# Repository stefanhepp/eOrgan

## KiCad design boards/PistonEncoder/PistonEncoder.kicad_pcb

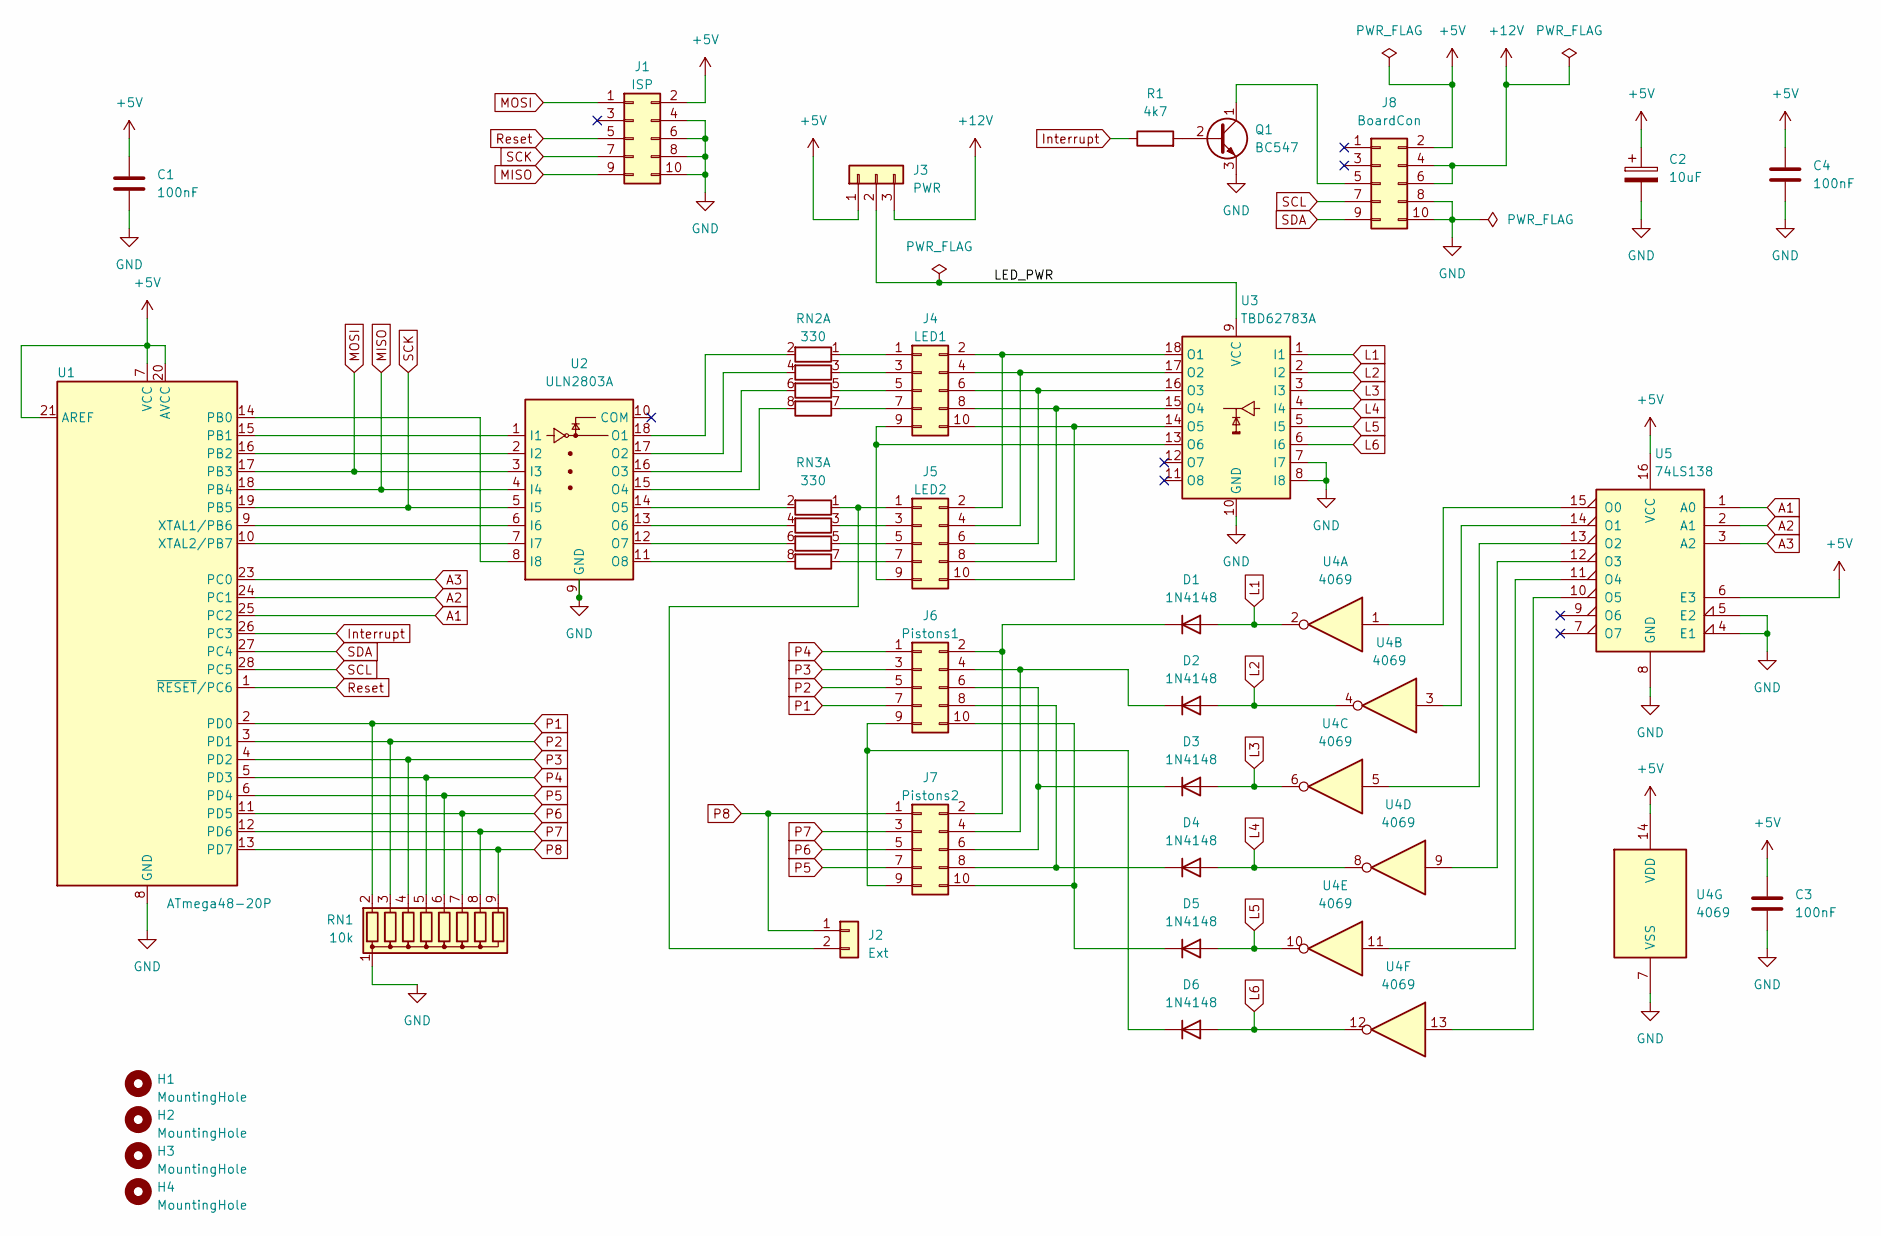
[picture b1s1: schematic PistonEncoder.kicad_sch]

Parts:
C1, C3, C4: 100nF; C_Disc_D4.3mm_W1.9mm_P5.00mm
C2: 10uF; C_Radial_D5.0mm_H11.0mm_P2.00mm
D1, D2, D3, D4, D5, D6: 1N4148; D_DO-35_SOD27_P7.62mm_Horizontal
H1, H2, H3, H4: MountingHole; MountingHole_3.2mm_M3
J1: ISP; IDC-Header_2x05_P2.54mm_Vertical
J2: Ext; PinHeader_1x02_P2.54mm_Vertical
J3: PWR; PinHeader_1x03_P2.54mm_Vertical
J4: LED1; IDC-Header_2x05_P2.54mm_Vertical
J5: LED2; IDC-Header_2x05_P2.54mm_Vertical
J6: Pistons1; IDC-Header_2x05_P2.54mm_Vertical
J7: Pistons2; IDC-Header_2x05_P2.54mm_Vertical
J8: BoardCon; IDC-Header_2x05_P2.54mm_Vertical
Q1: BC547; TO-92L_Inline_Wide
R1: 4k7; R_Axial_DIN0207_L6.3mm_D2.5mm_P10.16mm_Horizontal
RN1: 10k; R_Array_SIP9
RN2, RN3: 330; R_Array_SIP8
U1: ATmega48-20P; DIP-28_W7.62mm
U2: ULN2803A; DIP-18_W7.62mm
U3: TBD62783A; DIP-18_W7.62mm
U4: 4069; DIP-14_W7.62mm
U5: 74LS138; DIP-16_W7.62mm

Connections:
+5V: C1.1, C2.1, C3.1, C4.1, J1.2, J3.1, J8.2, U1.7 (VCC), U1.20 (AVCC), U1.21 (AREF), U4.14 (VDD), U5.6 (E3), U5.16 (VCC)
+12V: J3.3, J8.4, J8.6
/LED_PWR: J3.2, U3.9 (VCC)
A1: U1.25 (PC2), U5.1 (A0)
A2: U1.24 (PC1), U5.2 (A1)
A3: U1.23 (PC0), U5.3 (A2)
GND: C1.2, C2.2, C3.2, C4.2, J1.4, J1.6, J1.8, J1.10, J8.8, J8.10, Q1.3 (E), RN1.1 (common), U1.8 (GND), U1.22 (GND), U2.9 (GND), U3.7 (I7), U3.8 (I8), U3.10 (GND), U4.7 (VSS), U5.4 (E1), U5.5 (E2), U5.8 (GND)
Interrupt: R1.1, U1.26 (PC3)
L1: D1.2 (A), U3.1 (I1), U4.2
L2: D2.2 (A), U3.2 (I2), U4.4
L3: D3.2 (A), U3.3 (I3), U4.6
L4: D4.2 (A), U3.4 (I4), U4.8
L5: D5.2 (A), U3.5 (I5), U4.10
L6: D6.2 (A), U3.6 (I6), U4.12
MISO: J1.9, U1.18 (PB4), U2.4 (I4)
MOSI: J1.1, U1.17 (PB3), U2.3 (I3)
unnamed: D1.1 (K), J6.2, J7.2
unnamed: D2.1 (K), J6.4, J7.4
unnamed: D3.1 (K), J6.6, J7.6
unnamed: D4.1 (K), J6.8, J7.8
unnamed: D5.1 (K), J6.10, J7.10
unnamed: D6.1 (K), J6.9, J7.9
unnamed: J2.2, J5.1, RN3.1 (R1.1)
unnamed: J4.1, RN2.1 (R1.1)
unnamed: J4.2, J5.2, U3.18 (O1)
unnamed: J4.3, RN2.3 (R2.1)
unnamed: J4.4, J5.4, U3.17 (O2)
unnamed: J4.5, RN2.5 (R3.1)
unnamed: J4.6, J5.6, U3.16 (O3)
unnamed: J4.7, RN2.7 (R4.1)
unnamed: J4.8, J5.8, U3.15 (O4)
unnamed: J4.9, J5.9, U3.13 (O6)
unnamed: J4.10, J5.10, U3.14 (O5)
unnamed: J5.3, RN3.3 (R2.1)
unnamed: J5.5, RN3.5 (R3.1)
unnamed: J5.7, RN3.7 (R4.1)
unnamed: J8.5, Q1.1 (C)
unnamed: Q1.2 (B), R1.2
unnamed: RN2.2 (R1.2), U2.18 (O1)
unnamed: RN2.4 (R2.2), U2.17 (O2)
unnamed: RN2.6 (R3.2), U2.16 (O3)
unnamed: RN2.8 (R4.2), U2.15 (O4)
unnamed: RN3.2 (R1.2), U2.14 (O5)
unnamed: RN3.4 (R2.2), U2.13 (O6)
unnamed: RN3.6 (R3.2), U2.12 (O7)
unnamed: RN3.8 (R4.2), U2.11 (O8)
unnamed: U1.14 (PB0), U2.8 (I8)
unnamed: U1.15 (PB1), U2.1 (I1)
unnamed: U1.16 (PB2), U2.2 (I2)
unnamed: U1.9 (XTAL1/PB6), U2.6 (I6)
unnamed: U1.10 (XTAL2/PB7), U2.7 (I7)
unnamed: U4.1, U5.15 (O0)
unnamed: U4.3, U5.14 (O1)
unnamed: U4.5, U5.13 (O2)
unnamed: U4.9, U5.12 (O3)
unnamed: U4.11, U5.11 (O4)
unnamed: U4.13, U5.10 (O5)
P1: J6.7, RN1.2 (R1), U1.2 (PD0)
P2: J6.5, RN1.3 (R2), U1.3 (PD1)
P3: J6.3, RN1.4 (R3), U1.4 (PD2)
P4: J6.1, RN1.5 (R4), U1.5 (PD3)
P5: J7.7, RN1.6 (R5), U1.6 (PD4)
P6: J7.5, RN1.7 (R6), U1.11 (PD5)
P7: J7.3, RN1.8 (R7), U1.12 (PD6)
P8: J2.1, J7.1, RN1.9 (R8), U1.13 (PD7)
Reset: J1.5, U1.1 (~RESET/PC6)
SCK: J1.7, U1.19 (PB5), U2.5 (I5)
SCL: J8.7, U1.28 (PC5)
SDA: J8.9, U1.27 (PC4)

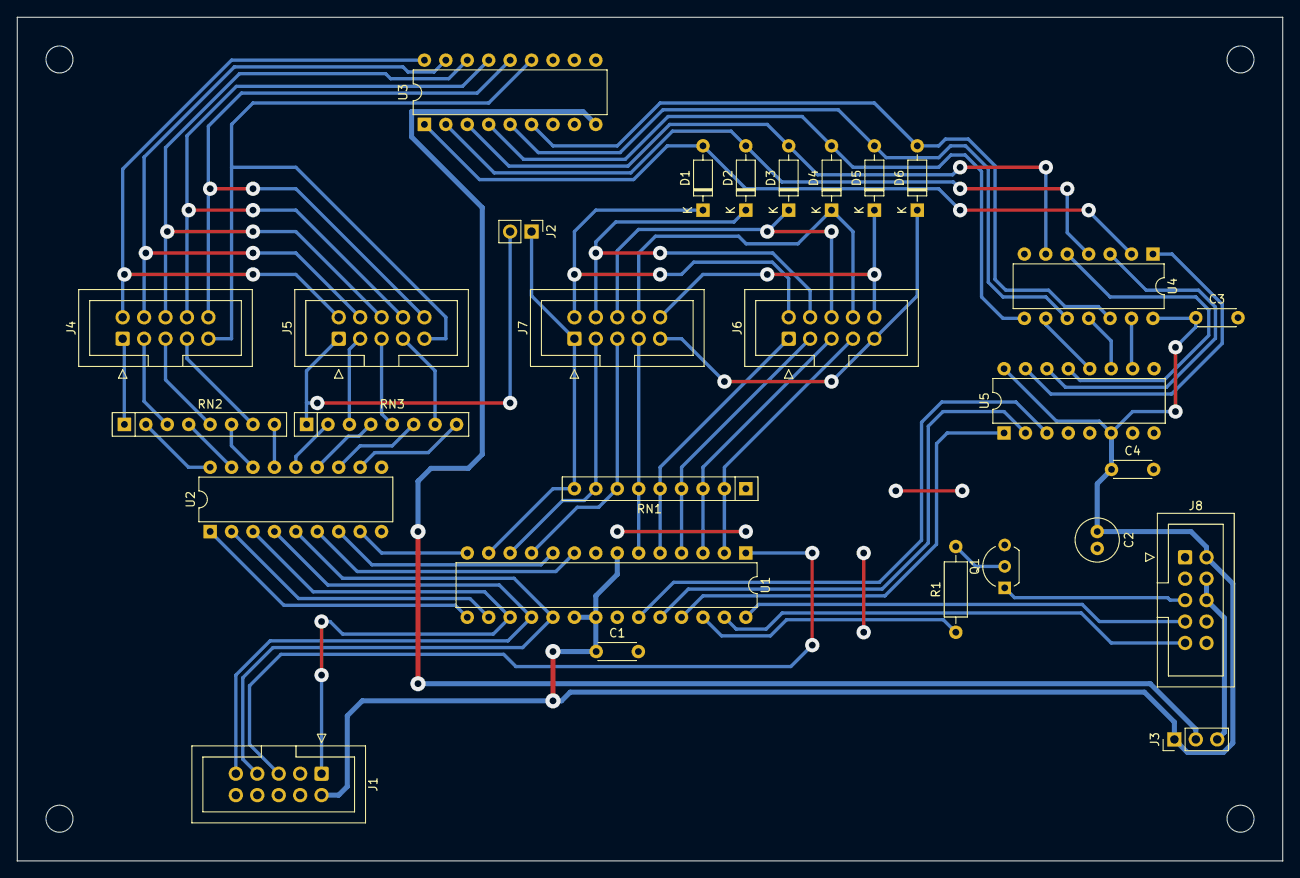
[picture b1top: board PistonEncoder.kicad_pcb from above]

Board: 2 copper layers, 150.0 x 100.0 mm, 32 parts (0 on the bottom side), 69 nets.

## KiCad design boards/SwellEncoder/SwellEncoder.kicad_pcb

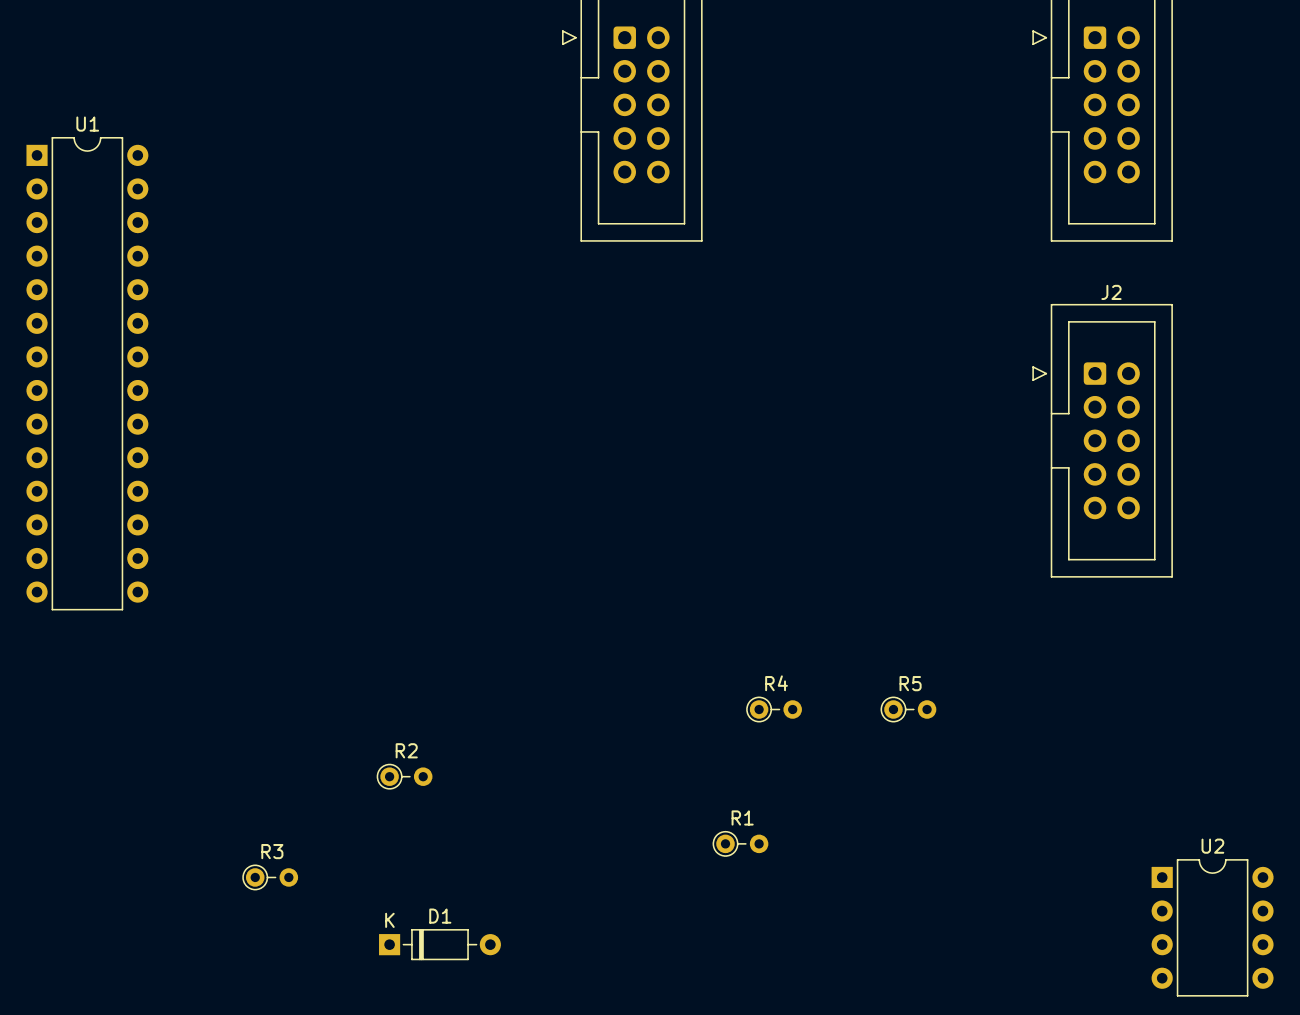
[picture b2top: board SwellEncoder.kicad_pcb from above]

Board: 2 copper layers, 11 parts (0 on the bottom side), 19 nets, no tracks yet.

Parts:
D1: 1N4148; D_DO-35_SOD27_P7.62mm_Horizontal
J2: ISP; IDC-Header_2x05_P2.54mm_Vertical
J3: ToeLeft; IDC-Header_2x05_P2.54mm_Vertical
J4: ToeRight; IDC-Header_2x05_P2.54mm_Vertical
R1: 10k; R_Axial_DIN0204_L3.6mm_D1.6mm_P2.54mm_Vertical
R2, R3, R4, R5: 220; R_Axial_DIN0204_L3.6mm_D1.6mm_P2.54mm_Vertical
U1: ATmega48-20P; DIP-28_W7.62mm
U2: 6N138; DIP-8_W7.62mm

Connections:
+5V: J2.2, R1.1, R4.2, U1.7 (VCC), U1.20 (AVCC), U1.21 (AREF), U2.8 (VCC)
GND: J2.4, J2.6, J2.8, J2.10, U1.8 (GND), U1.22 (GND), U2.5 (GND)
Interrupt: R2.1, U1.26 (PC3)
L1: J4.10, U1.14 (PB0)
L2: J4.8, U1.15 (PB1)
L3: J3.10, U1.16 (PB2)
MISO: J2.9, U1.18 (PB4)
MOSI: J2.1, J3.8, U1.17 (PB3)
unnamed: D1.1 (K), R5.2, U2.2 (C1)
unnamed: D1.2 (A), U2.3 (C2)
unnamed: J3.1, J4.1, U1.5 (PD3)
unnamed: J3.3, J4.3, U1.6 (PD4)
unnamed: J3.5, J4.5, U1.11 (PD5)
unnamed: J3.7, J4.7, U1.12 (PD6)
unnamed: J3.9, J4.9, U1.13 (PD7)
RXD: R1.2, U1.2 (PD0), U2.6 (VO2)
Reset: J2.5, U1.1 (~RESET/PC6)
SCK: J2.7, U1.19 (PB5)
TXD: R3.1, U1.3 (PD1)

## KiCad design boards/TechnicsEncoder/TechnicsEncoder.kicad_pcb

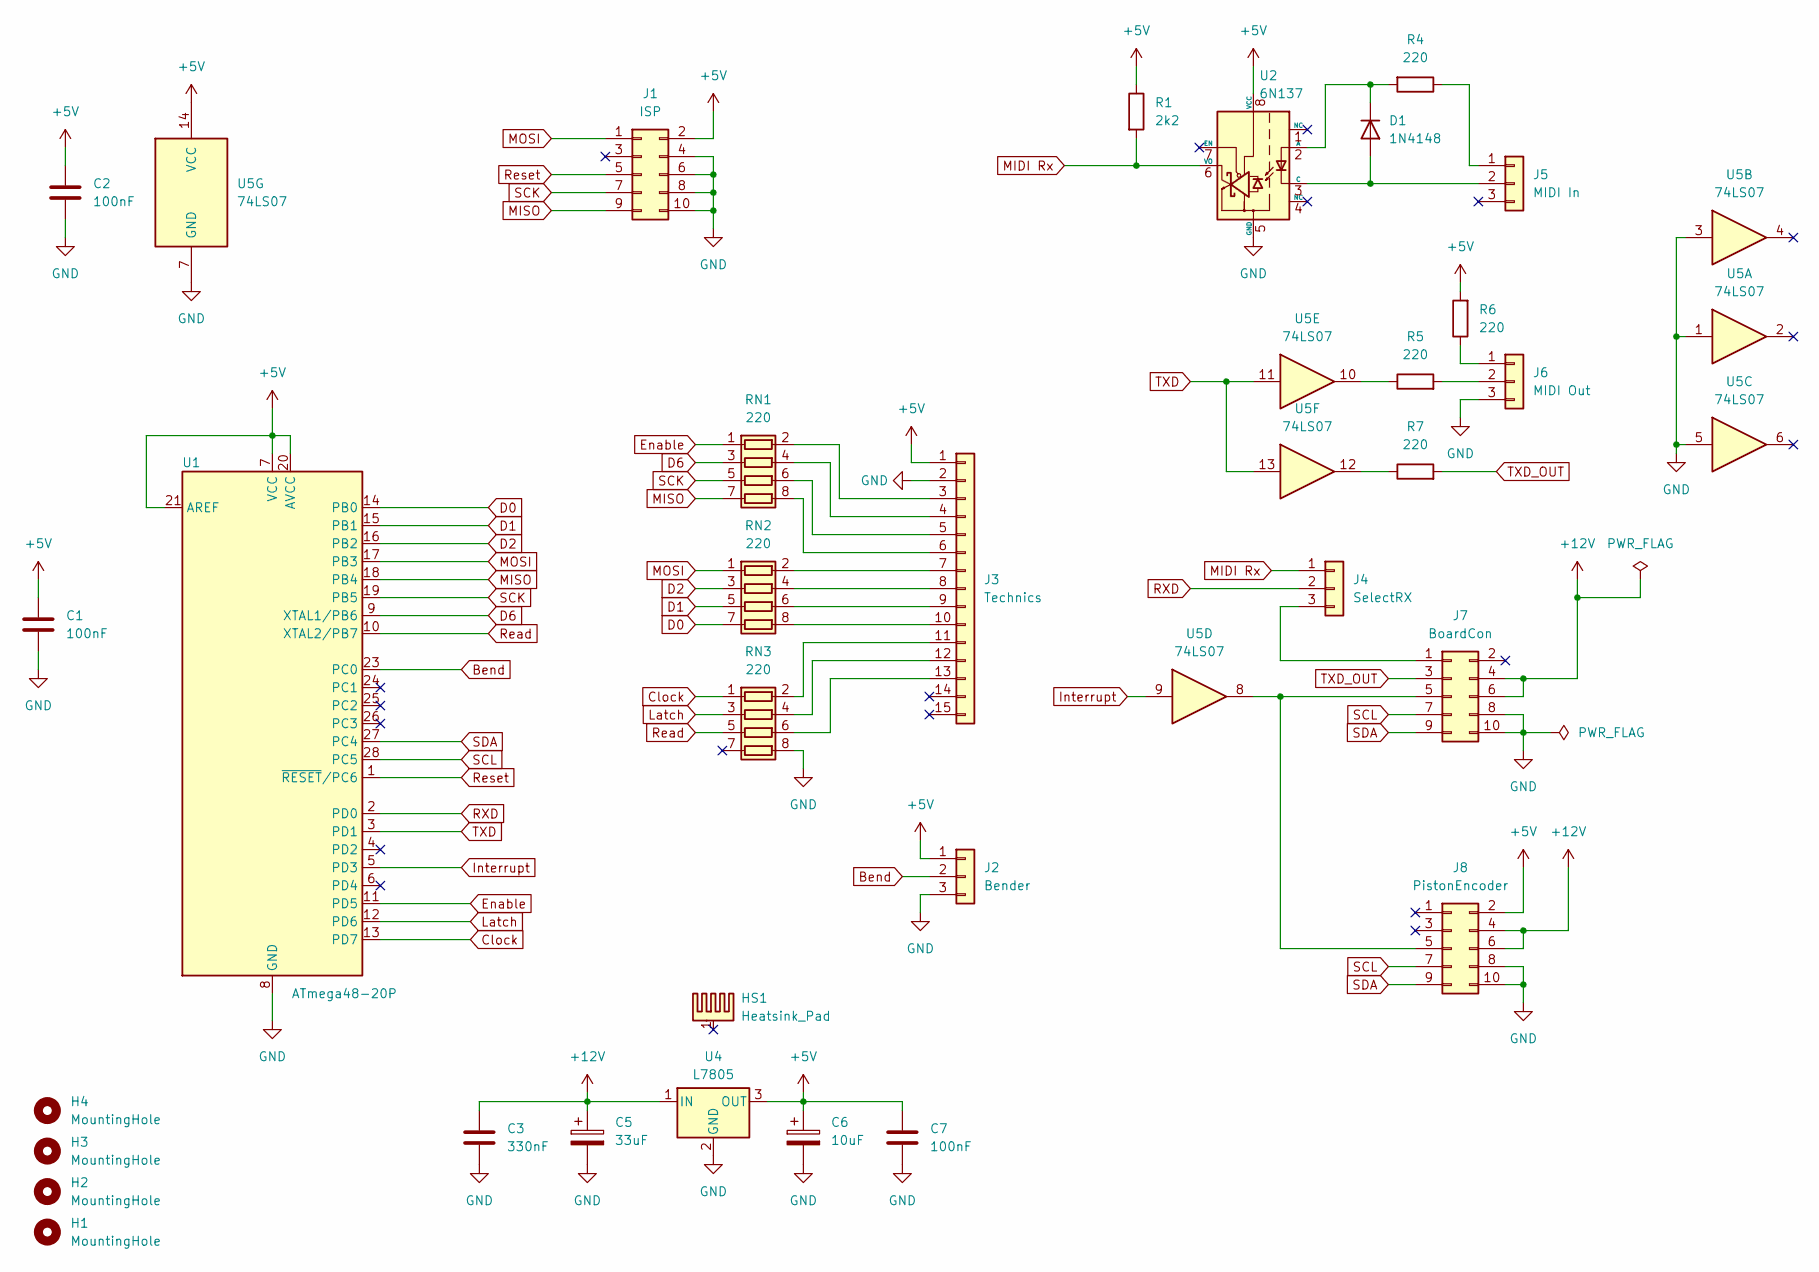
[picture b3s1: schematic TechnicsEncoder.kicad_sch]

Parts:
C1, C2, C7: 100nF; C_Disc_D4.3mm_W1.9mm_P5.00mm
C3: 330nF; C_Disc_D4.3mm_W1.9mm_P5.00mm
C5: 33uF; CP_Radial_D7.5mm_P2.50mm
C6: 10uF; CP_Radial_D6.3mm_P2.50mm
D1: 1N4148; D_DO-35_SOD27_P7.62mm_Horizontal
H1, H2, H3, H4: MountingHole; MountingHole_3mm
HS1: Heatsink_Pad; Heatsink_Aavid_TO-220_H12.7mm
J1: ISP; IDC-Header_2x05_P2.54mm_Vertical
J2: Bender; PinHeader_1x03_P2.54mm_Vertical
J3: Technics; JST_PH_B15B-PH-K_1x15_P2.00mm_Vertical
J4: SelectRX; PinHeader_1x03_P2.54mm_Vertical
J5: MIDI In; PinHeader_1x03_P2.54mm_Vertical
J6: MIDI Out; PinHeader_1x03_P2.54mm_Vertical
J7: BoardCon; IDC-Header_2x05_P2.54mm_Vertical
J8: PistonEncoder; IDC-Header_2x05_P2.54mm_Vertical
R1: 2k2; R_Axial_DIN0207_L6.3mm_D2.5mm_P2.54mm_Vertical
R4, R6: 220; R_Axial_DIN0207_L6.3mm_D2.5mm_P2.54mm_Vertical
R5, R7: 220; R_Axial_DIN0207_L6.3mm_D2.5mm_P10.16mm_Horizontal
RN1, RN2, RN3: 220; R_Array_SIP8
U1: ATmega48-20P; DIP-28_W7.62mm_Socket
U2: 6N137; DIP-8_W7.62mm
U4: L7805; TO-220-3_Vertical
U5: 74LS07; DIP-14_W7.62mm

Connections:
+5V: C1.1, C2.1, C6.1, C7.1, J1.2, J2.1, J3.1, J8.2, R1.1, R6.2, U1.7 (VCC), U1.20 (AVCC), U1.21 (AREF), U2.8 (VCC), U4.3 (OUT), U5.14 (VCC)
+12V: C3.1, C5.1, J7.4, J7.6, J8.4, J8.6, U4.1 (IN)
Bend: J2.2, U1.23 (PC0)
Clock: RN3.1 (R1.1), U1.13 (PD7)
D0: RN2.7 (R4.1), U1.14 (PB0)
D1: RN2.5 (R3.1), U1.15 (PB1)
D2: RN2.3 (R2.1), U1.16 (PB2)
D6: RN1.3 (R2.1), U1.9 (XTAL1/PB6)
Enable: RN1.1 (R1.1), U1.11 (PD5)
GND: C1.2, C2.2, C3.2, C5.2, C6.2, C7.2, J1.4, J1.6, J1.8, J1.10, J2.3, J3.2, J6.3, J7.8, J7.10, J8.8, J8.10, RN3.8 (R4.2), U1.8 (GND), U1.22 (GND), U2.5 (GND), U4.2 (GND), U5.1, U5.3, U5.5, U5.7 (GND)
Interrupt: U1.5 (PD3), U5.9
Latch: RN3.3 (R2.1), U1.12 (PD6)
MIDI Rx: J4.1, R1.2, U2.6 (VO)
MISO: J1.9, RN1.7 (R4.1), U1.18 (PB4)
MOSI: J1.1, RN2.1 (R1.1), U1.17 (PB3)
unnamed: D1.2 (A), J5.2, U2.3 (C)
unnamed: D1.1 (K), R4.2, U2.2 (A)
unnamed: J3.3, RN1.2 (R1.2)
unnamed: J3.4, RN1.4 (R2.2)
unnamed: J3.5, RN1.6 (R3.2)
unnamed: J3.6, RN1.8 (R4.2)
unnamed: J3.7, RN2.2 (R1.2)
unnamed: J3.8, RN2.4 (R2.2)
unnamed: J3.9, RN2.6 (R3.2)
unnamed: J3.10, RN2.8 (R4.2)
unnamed: J3.11, RN3.2 (R1.2)
unnamed: J3.12, RN3.4 (R2.2)
unnamed: J3.13, RN3.6 (R3.2)
unnamed: J4.3, J7.1
unnamed: J5.1, R4.1
unnamed: J6.1, R6.1
unnamed: J6.2, R5.2
unnamed: J7.5, J8.5, U5.8
unnamed: R5.1, U5.10
unnamed: R7.1, U5.12
RXD: J4.2, U1.2 (PD0)
Read: RN3.5 (R3.1), U1.10 (XTAL2/PB7)
Reset: J1.5, U1.1 (~RESET/PC6)
SCK: J1.7, RN1.5 (R3.1), U1.19 (PB5)
SCL: J7.7, J8.7, U1.28 (PC5)
SDA: J7.9, J8.9, U1.27 (PC4)
TXD: U1.3 (PD1), U5.11, U5.13
TXD_OUT: J7.3, R7.2

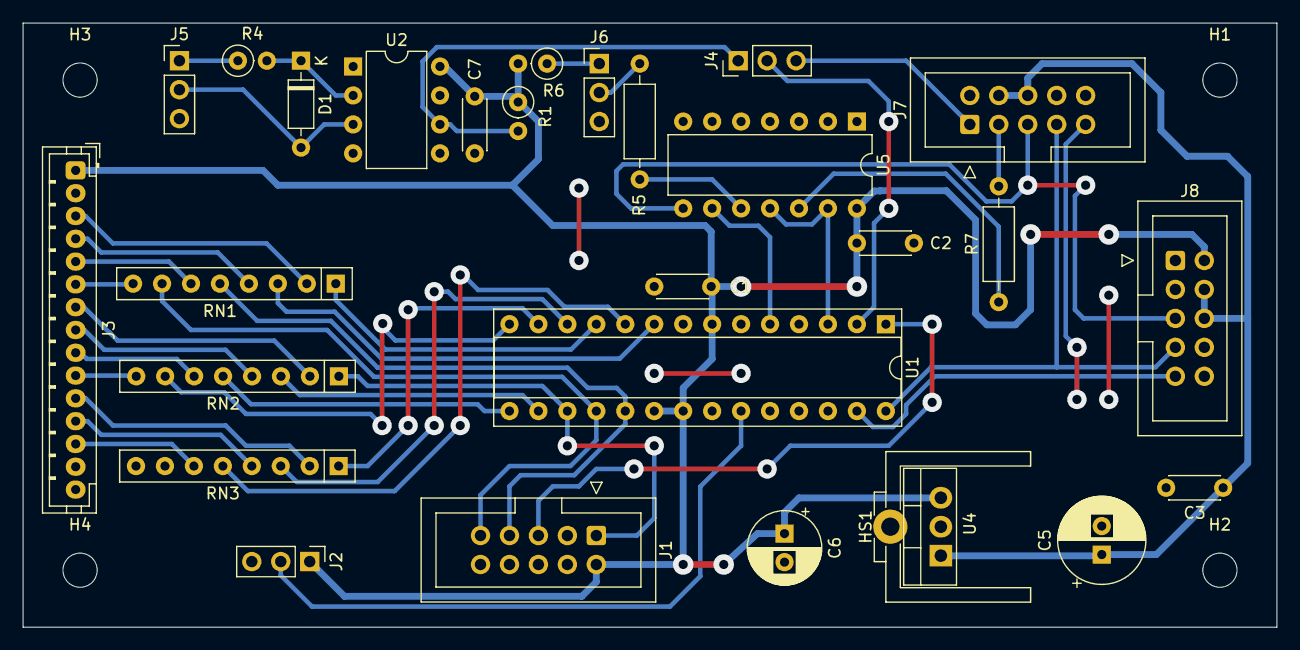
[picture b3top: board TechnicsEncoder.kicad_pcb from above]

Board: 2 copper layers, 110.0 x 53.0 mm, 32 parts (0 on the bottom side), 43 nets.
